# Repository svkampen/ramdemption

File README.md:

# Cyberslak PowerRAM 10MB

A 10MB RAM expansion card for the PowerBook 165c.

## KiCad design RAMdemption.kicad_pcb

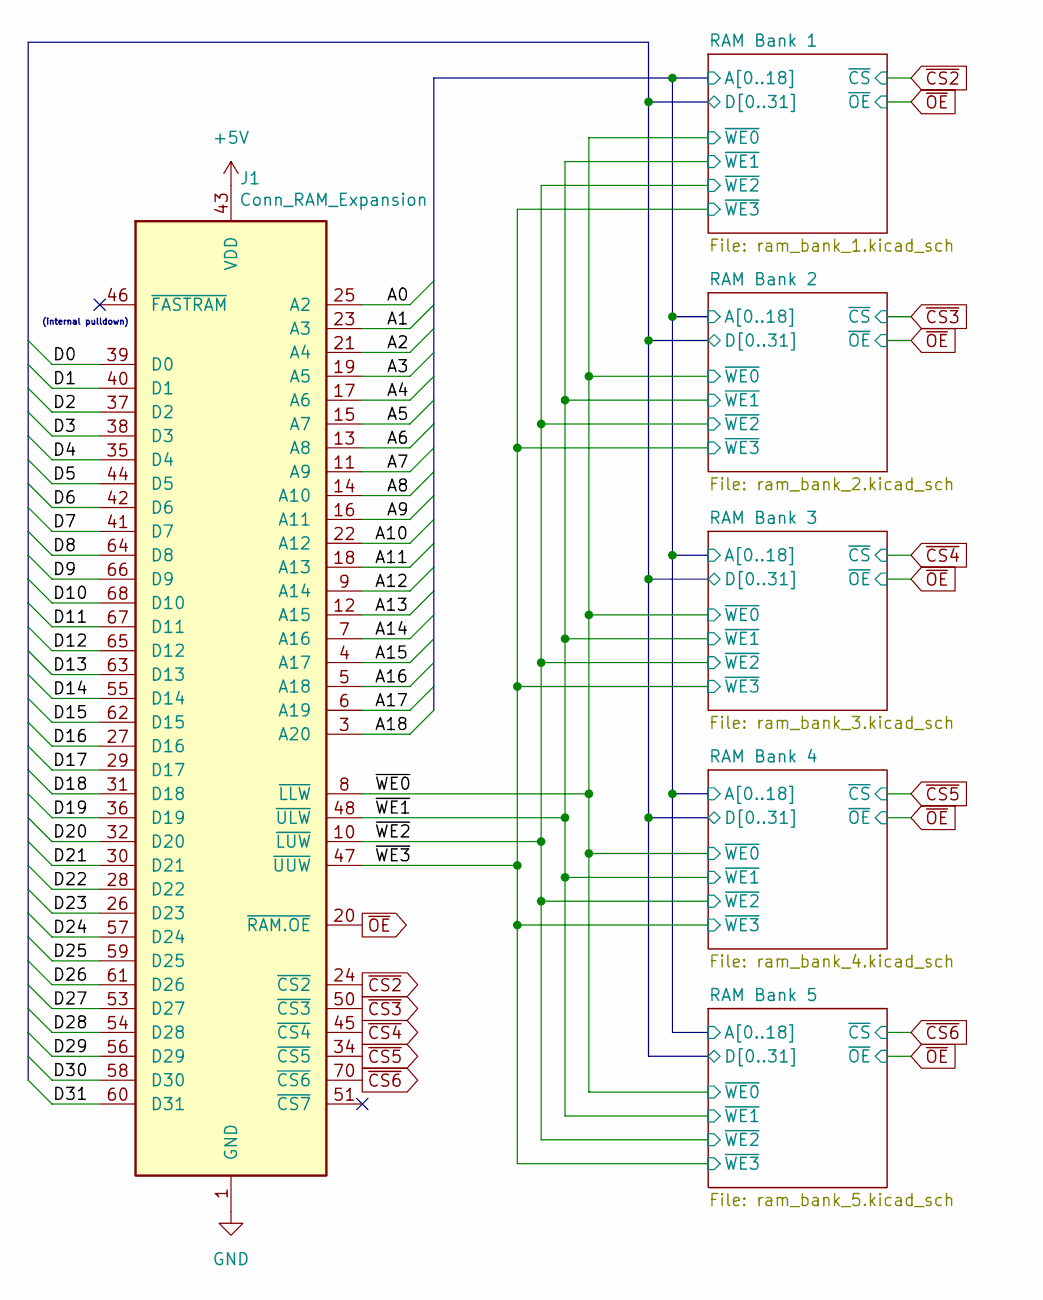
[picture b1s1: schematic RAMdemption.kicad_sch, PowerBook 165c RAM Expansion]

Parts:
J1: Conn_RAM_Expansion; TE_5-104652-7_NoHoles

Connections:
+5V: J1.43 (VDD), J1.52 (VDD); also elsewhere on the board
/RAM Bank 1/A0: J1.25 (A2); also elsewhere on the board
/RAM Bank 1/A1: J1.23 (A3); also elsewhere on the board
/RAM Bank 1/A2: J1.21 (A4); also elsewhere on the board
/RAM Bank 1/A3: J1.19 (A5); also elsewhere on the board
/RAM Bank 1/A4: J1.17 (A6); also elsewhere on the board
/RAM Bank 1/A5: J1.15 (A7); also elsewhere on the board
/RAM Bank 1/A6: J1.13 (A8); also elsewhere on the board
/RAM Bank 1/A7: J1.11 (A9); also elsewhere on the board
/RAM Bank 1/A8: J1.14 (A10); also elsewhere on the board
/RAM Bank 1/A9: J1.16 (A11); also elsewhere on the board
/RAM Bank 1/A10: J1.22 (A12); also elsewhere on the board
/RAM Bank 1/A11: J1.18 (A13); also elsewhere on the board
/RAM Bank 1/A12: J1.9 (A14); also elsewhere on the board
/RAM Bank 1/A13: J1.12 (A15); also elsewhere on the board
/RAM Bank 1/A14: J1.7 (A16); also elsewhere on the board
/RAM Bank 1/A15: J1.4 (A17); also elsewhere on the board
/RAM Bank 1/A16: J1.5 (A18); also elsewhere on the board
/RAM Bank 1/A17: J1.6 (A19); also elsewhere on the board
/RAM Bank 1/A18: J1.3 (A20); also elsewhere on the board
/RAM Bank 1/D0: J1.39 (D0); also elsewhere on the board
/RAM Bank 1/D1: J1.40 (D1); also elsewhere on the board
/RAM Bank 1/D2: J1.37 (D2); also elsewhere on the board
/RAM Bank 1/D3: J1.38 (D3); also elsewhere on the board
/RAM Bank 1/D4: J1.35 (D4); also elsewhere on the board
/RAM Bank 1/D5: J1.44 (D5); also elsewhere on the board
/RAM Bank 1/D6: J1.42 (D6); also elsewhere on the board
/RAM Bank 1/D7: J1.41 (D7); also elsewhere on the board
/RAM Bank 1/D8: J1.64 (D8); also elsewhere on the board
/RAM Bank 1/D9: J1.66 (D9); also elsewhere on the board
/RAM Bank 1/D10: J1.68 (D10); also elsewhere on the board
/RAM Bank 1/D11: J1.67 (D11); also elsewhere on the board
/RAM Bank 1/D12: J1.65 (D12); also elsewhere on the board
/RAM Bank 1/D13: J1.63 (D13); also elsewhere on the board
/RAM Bank 1/D14: J1.55 (D14); also elsewhere on the board
/RAM Bank 1/D15: J1.62 (D15); also elsewhere on the board
/RAM Bank 1/D16: J1.27 (D16); also elsewhere on the board
/RAM Bank 1/D17: J1.29 (D17); also elsewhere on the board
/RAM Bank 1/D18: J1.31 (D18); also elsewhere on the board
/RAM Bank 1/D19: J1.36 (D19); also elsewhere on the board
/RAM Bank 1/D20: J1.32 (D20); also elsewhere on the board
/RAM Bank 1/D21: J1.30 (D21); also elsewhere on the board
/RAM Bank 1/D22: J1.28 (D22); also elsewhere on the board
/RAM Bank 1/D23: J1.26 (D23); also elsewhere on the board
/RAM Bank 1/D24: J1.57 (D24); also elsewhere on the board
/RAM Bank 1/D25: J1.59 (D25); also elsewhere on the board
/RAM Bank 1/D26: J1.61 (D26); also elsewhere on the board
/RAM Bank 1/D27: J1.53 (D27); also elsewhere on the board
/RAM Bank 1/D28: J1.54 (D28); also elsewhere on the board
/RAM Bank 1/D29: J1.56 (D29); also elsewhere on the board
/RAM Bank 1/D30: J1.58 (D30); also elsewhere on the board
/RAM Bank 1/D31: J1.60 (D31); also elsewhere on the board
/~WE0: J1.8 (~LLW); also elsewhere on the board
/~WE1: J1.48 (~ULW); also elsewhere on the board
/~WE2: J1.10 (~LUW); also elsewhere on the board
/~WE3: J1.47 (~UUW); also elsewhere on the board
GND: J1.1 (GND), J1.2 (GND), J1.33 (GND), J1.69 (GND); also elsewhere on the board
~CS2: J1.24 (~CS2); also elsewhere on the board
~CS3: J1.50 (~CS3); also elsewhere on the board
~CS4: J1.45 (~CS4); also elsewhere on the board
~CS5: J1.34 (~CS5); also elsewhere on the board
~CS6: J1.70 (~CS6); also elsewhere on the board
~OE: J1.20 (~RAM.OE); also elsewhere on the board

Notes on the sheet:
(internal pulldown)

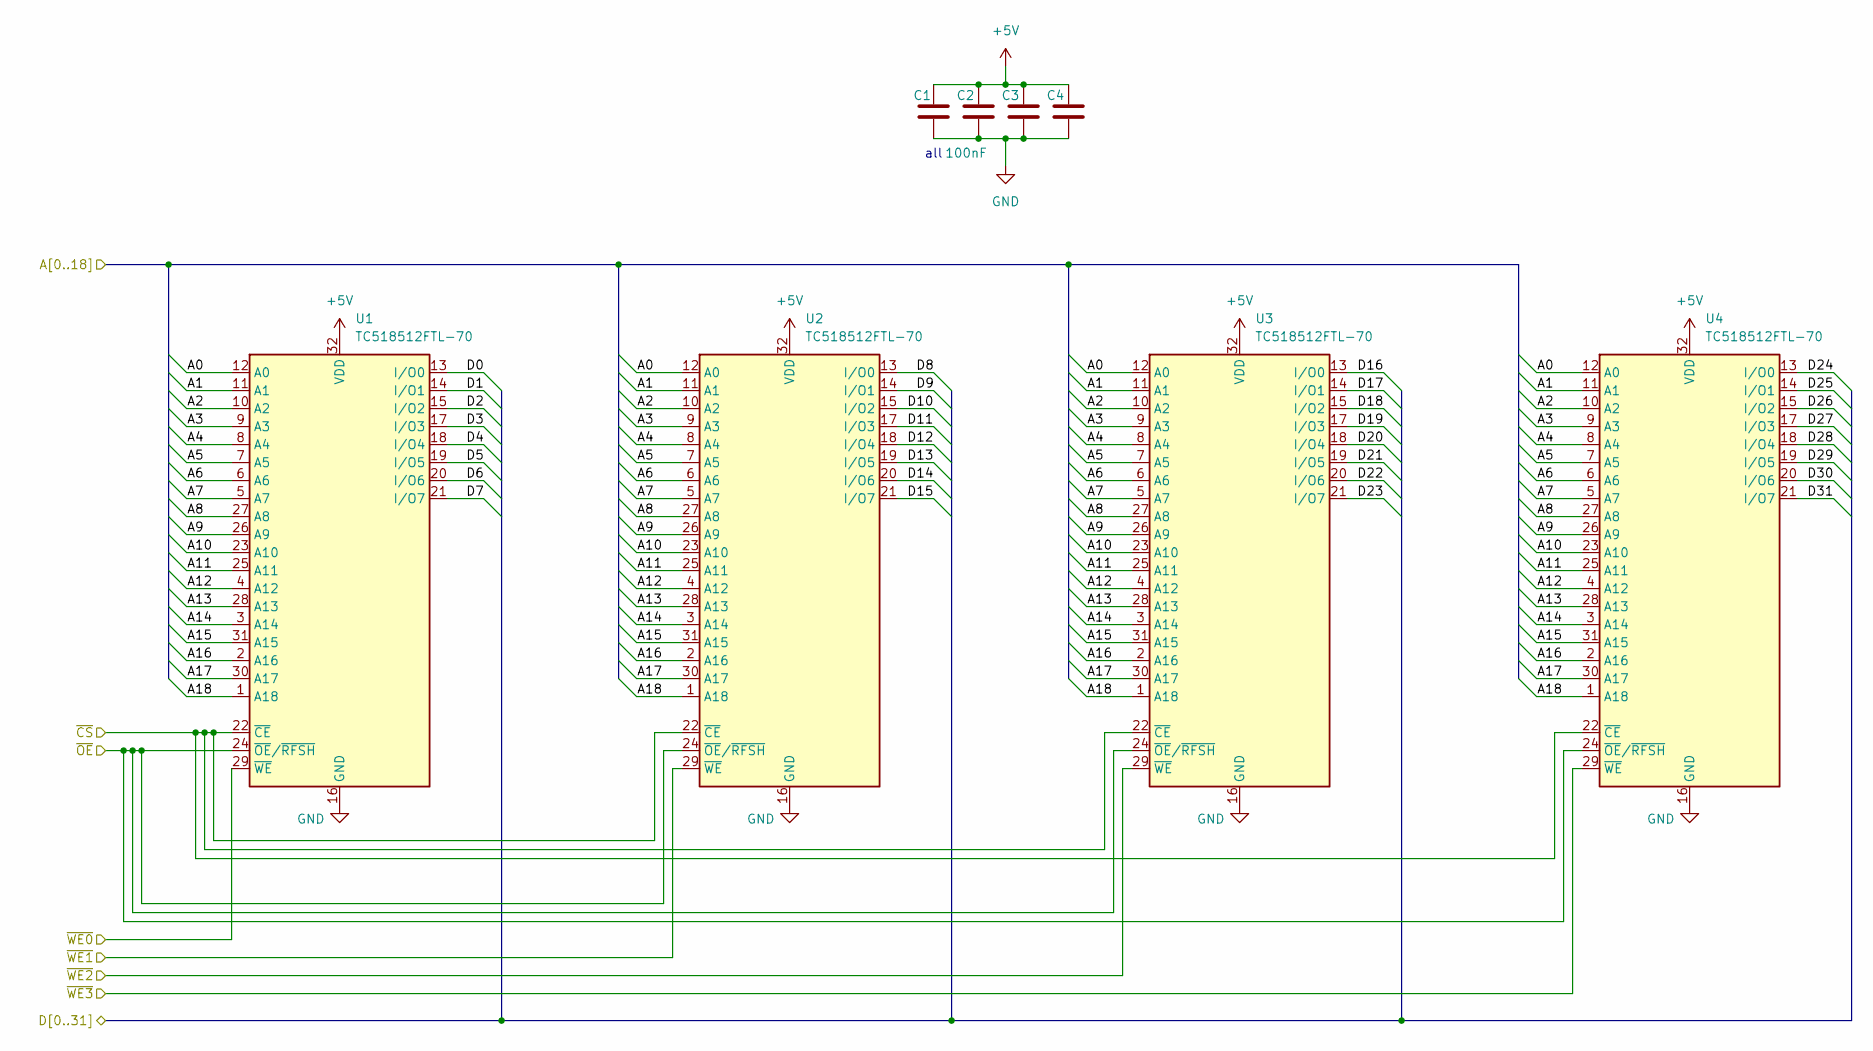
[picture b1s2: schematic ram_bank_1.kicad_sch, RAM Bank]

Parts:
C1, C2, C3, C4: 100nF; C_0805_2012Metric_Pad1.18x1.45mm_HandSolder
U1: TC518512FTL-70; TSOP-II-32_Data0
U2: TC518512FTL-70; TSOP-II-32_ReversedAddr
U3: TC518512FTL-70; TSOP-II-32_21.0x10.2mm_P1.27mm
U4: TC518512FTL-70; TSOP-II-32_ReversedAddr_Data3

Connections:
+5V: C1.1, C2.1, C3.1, C4.1, U1.32 (VDD), U2.32 (VDD), U3.32 (VDD), U4.32 (VDD); also elsewhere on the board
/RAM Bank 1/A0: U1.12 (A0), U2.12 (A0), U3.12 (A0), U4.12 (A0); also elsewhere on the board
/RAM Bank 1/A1: U1.11 (A1), U2.11 (A1), U3.11 (A1), U4.11 (A1); also elsewhere on the board
/RAM Bank 1/A2: U1.10 (A2), U2.10 (A2), U3.10 (A2), U4.10 (A2); also elsewhere on the board
/RAM Bank 1/A3: U1.9 (A3), U2.9 (A3), U3.9 (A3), U4.9 (A3); also elsewhere on the board
/RAM Bank 1/A4: U1.8 (A4), U2.8 (A4), U3.8 (A4), U4.8 (A4); also elsewhere on the board
/RAM Bank 1/A5: U1.7 (A5), U2.7 (A5), U3.7 (A5), U4.7 (A5); also elsewhere on the board
/RAM Bank 1/A6: U1.6 (A6), U2.6 (A6), U3.6 (A6), U4.6 (A6); also elsewhere on the board
/RAM Bank 1/A7: U1.5 (A7), U2.5 (A7), U3.5 (A7), U4.5 (A7); also elsewhere on the board
/RAM Bank 1/A8: U1.27 (A8), U2.27 (A8), U3.27 (A8), U4.27 (A8); also elsewhere on the board
/RAM Bank 1/A9: U1.26 (A9), U2.26 (A9), U3.26 (A9), U4.26 (A9); also elsewhere on the board
/RAM Bank 1/A10: U1.23 (A10), U2.23 (A10), U3.23 (A10), U4.23 (A10); also elsewhere on the board
/RAM Bank 1/A11: U1.25 (A11), U2.25 (A11), U3.25 (A11), U4.25 (A11); also elsewhere on the board
/RAM Bank 1/A12: U1.4 (A12), U2.4 (A12), U3.4 (A12), U4.4 (A12); also elsewhere on the board
/RAM Bank 1/A13: U1.28 (A13), U2.28 (A13), U3.28 (A13), U4.28 (A13); also elsewhere on the board
/RAM Bank 1/A14: U1.3 (A14), U2.3 (A14), U3.3 (A14), U4.3 (A14); also elsewhere on the board
/RAM Bank 1/A15: U1.31 (A15), U2.31 (A15), U3.31 (A15), U4.31 (A15); also elsewhere on the board
/RAM Bank 1/A16: U1.2 (A16), U2.2 (A16), U3.2 (A16), U4.2 (A16); also elsewhere on the board
/RAM Bank 1/A17: U1.30 (A17), U2.30 (A17), U3.30 (A17), U4.30 (A17); also elsewhere on the board
/RAM Bank 1/A18: U1.1 (A18), U2.1 (A18), U3.1 (A18), U4.1 (A18); also elsewhere on the board
/RAM Bank 1/D0: U1.13 (I/O0); also elsewhere on the board
/RAM Bank 1/D1: U1.14 (I/O1); also elsewhere on the board
/RAM Bank 1/D2: U1.15 (I/O2); also elsewhere on the board
/RAM Bank 1/D3: U1.17 (I/O3); also elsewhere on the board
/RAM Bank 1/D4: U1.18 (I/O4); also elsewhere on the board
/RAM Bank 1/D5: U1.19 (I/O5); also elsewhere on the board
/RAM Bank 1/D6: U1.20 (I/O6); also elsewhere on the board
/RAM Bank 1/D7: U1.21 (I/O7); also elsewhere on the board
/RAM Bank 1/D8: U2.13 (I/O0); also elsewhere on the board
/RAM Bank 1/D9: U2.14 (I/O1); also elsewhere on the board
/RAM Bank 1/D10: U2.15 (I/O2); also elsewhere on the board
/RAM Bank 1/D11: U2.17 (I/O3); also elsewhere on the board
/RAM Bank 1/D12: U2.18 (I/O4); also elsewhere on the board
/RAM Bank 1/D13: U2.19 (I/O5); also elsewhere on the board
/RAM Bank 1/D14: U2.20 (I/O6); also elsewhere on the board
/RAM Bank 1/D15: U2.21 (I/O7); also elsewhere on the board
/RAM Bank 1/D16: U3.13 (I/O0); also elsewhere on the board
/RAM Bank 1/D17: U3.14 (I/O1); also elsewhere on the board
/RAM Bank 1/D18: U3.15 (I/O2); also elsewhere on the board
/RAM Bank 1/D19: U3.17 (I/O3); also elsewhere on the board
/RAM Bank 1/D20: U3.18 (I/O4); also elsewhere on the board
/RAM Bank 1/D21: U3.19 (I/O5); also elsewhere on the board
/RAM Bank 1/D22: U3.20 (I/O6); also elsewhere on the board
/RAM Bank 1/D23: U3.21 (I/O7); also elsewhere on the board
/RAM Bank 1/D24: U4.13 (I/O0); also elsewhere on the board
/RAM Bank 1/D25: U4.14 (I/O1); also elsewhere on the board
/RAM Bank 1/D26: U4.15 (I/O2); also elsewhere on the board
/RAM Bank 1/D27: U4.17 (I/O3); also elsewhere on the board
/RAM Bank 1/D28: U4.18 (I/O4); also elsewhere on the board
/RAM Bank 1/D29: U4.19 (I/O5); also elsewhere on the board
/RAM Bank 1/D30: U4.20 (I/O6); also elsewhere on the board
/RAM Bank 1/D31: U4.21 (I/O7); also elsewhere on the board
/~WE0: U1.29 (~WE); also elsewhere on the board
/~WE1: U2.29 (~WE); also elsewhere on the board
/~WE2: U3.29 (~WE); also elsewhere on the board
/~WE3: U4.29 (~WE); also elsewhere on the board
GND: C1.2, C2.2, C3.2, C4.2, U1.16 (GND), U2.16 (GND), U3.16 (GND), U4.16 (GND); also elsewhere on the board
~CS2: U1.22 (~CE), U2.22 (~CE), U3.22 (~CE), U4.22 (~CE); also elsewhere on the board
~OE: U1.24 (~OE/~RFSH), U2.24 (~OE/~RFSH), U3.24 (~OE/~RFSH), U4.24 (~OE/~RFSH); also elsewhere on the board

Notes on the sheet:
all

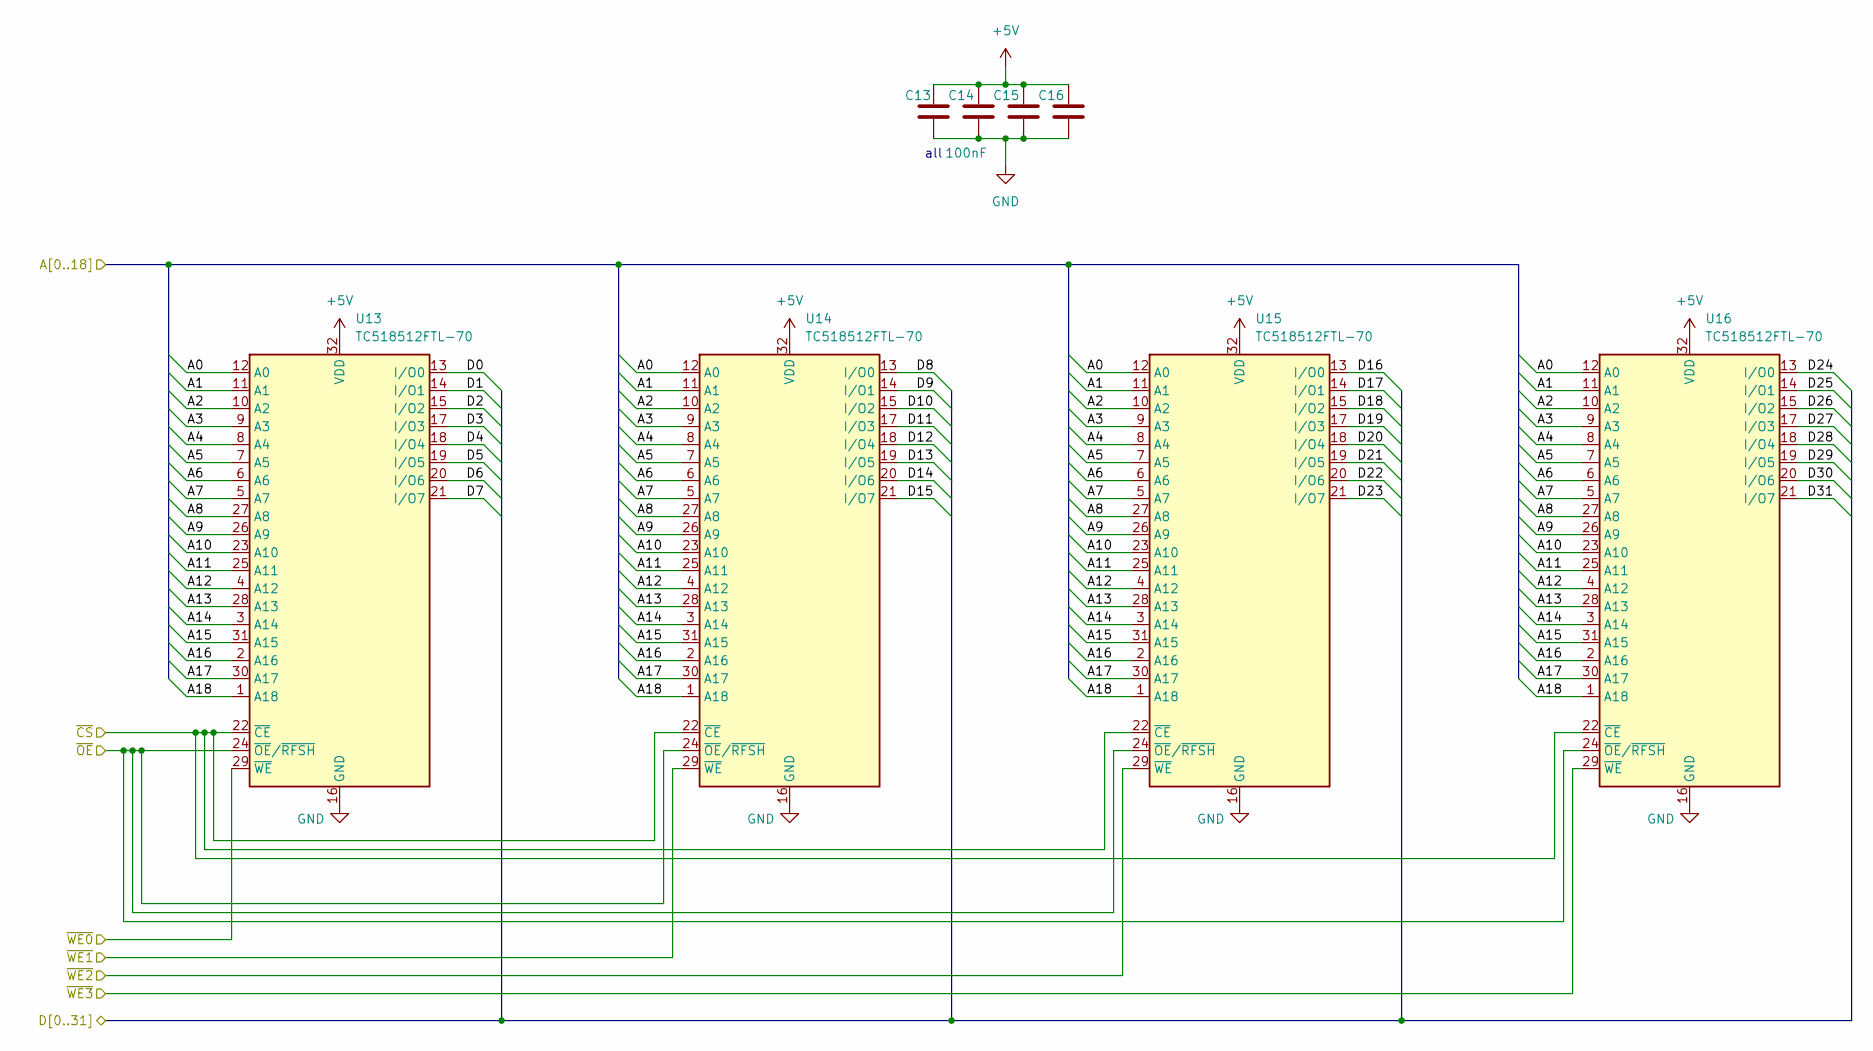
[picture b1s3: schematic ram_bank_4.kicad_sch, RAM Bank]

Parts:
C13, C14, C15, C16: 100nF; C_0805_2012Metric_Pad1.18x1.45mm_HandSolder
U13: TC518512FTL-70; TSOP-II-32_Data0
U14: TC518512FTL-70; TSOP-II-32_ReversedAddr
U15: TC518512FTL-70; TSOP-II-32_21.0x10.2mm_P1.27mm
U16: TC518512FTL-70; TSOP-II-NormalAddr-Data3

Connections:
+5V: C13.1, C14.1, C15.1, C16.1, U13.32 (VDD), U14.32 (VDD), U15.32 (VDD), U16.32 (VDD); also elsewhere on the board
/RAM Bank 1/A0: U13.12 (A0), U14.12 (A0), U15.12 (A0), U16.12 (A0); also elsewhere on the board
/RAM Bank 1/A1: U13.11 (A1), U14.11 (A1), U15.11 (A1), U16.11 (A1); also elsewhere on the board
/RAM Bank 1/A2: U13.10 (A2), U14.10 (A2), U15.10 (A2), U16.10 (A2); also elsewhere on the board
/RAM Bank 1/A3: U13.9 (A3), U14.9 (A3), U15.9 (A3), U16.9 (A3); also elsewhere on the board
/RAM Bank 1/A4: U13.8 (A4), U14.8 (A4), U15.8 (A4), U16.8 (A4); also elsewhere on the board
/RAM Bank 1/A5: U13.7 (A5), U14.7 (A5), U15.7 (A5), U16.7 (A5); also elsewhere on the board
/RAM Bank 1/A6: U13.6 (A6), U14.6 (A6), U15.6 (A6), U16.6 (A6); also elsewhere on the board
/RAM Bank 1/A7: U13.5 (A7), U14.5 (A7), U15.5 (A7), U16.5 (A7); also elsewhere on the board
/RAM Bank 1/A8: U13.27 (A8), U14.27 (A8), U15.27 (A8), U16.27 (A8); also elsewhere on the board
/RAM Bank 1/A9: U13.26 (A9), U14.26 (A9), U15.26 (A9), U16.26 (A9); also elsewhere on the board
/RAM Bank 1/A10: U13.23 (A10), U14.23 (A10), U15.23 (A10), U16.23 (A10); also elsewhere on the board
/RAM Bank 1/A11: U13.25 (A11), U14.25 (A11), U15.25 (A11), U16.25 (A11); also elsewhere on the board
/RAM Bank 1/A12: U13.4 (A12), U14.4 (A12), U15.4 (A12), U16.4 (A12); also elsewhere on the board
/RAM Bank 1/A13: U13.28 (A13), U14.28 (A13), U15.28 (A13), U16.28 (A13); also elsewhere on the board
/RAM Bank 1/A14: U13.3 (A14), U14.3 (A14), U15.3 (A14), U16.3 (A14); also elsewhere on the board
/RAM Bank 1/A15: U13.31 (A15), U14.31 (A15), U15.31 (A15), U16.31 (A15); also elsewhere on the board
/RAM Bank 1/A16: U13.2 (A16), U14.2 (A16), U15.2 (A16), U16.2 (A16); also elsewhere on the board
/RAM Bank 1/A17: U13.30 (A17), U14.30 (A17), U15.30 (A17), U16.30 (A17); also elsewhere on the board
/RAM Bank 1/A18: U13.1 (A18), U14.1 (A18), U15.1 (A18), U16.1 (A18); also elsewhere on the board
/RAM Bank 1/D0: U13.13 (I/O0); also elsewhere on the board
/RAM Bank 1/D1: U13.14 (I/O1); also elsewhere on the board
/RAM Bank 1/D2: U13.15 (I/O2); also elsewhere on the board
/RAM Bank 1/D3: U13.17 (I/O3); also elsewhere on the board
/RAM Bank 1/D4: U13.18 (I/O4); also elsewhere on the board
/RAM Bank 1/D5: U13.19 (I/O5); also elsewhere on the board
/RAM Bank 1/D6: U13.20 (I/O6); also elsewhere on the board
/RAM Bank 1/D7: U13.21 (I/O7); also elsewhere on the board
/RAM Bank 1/D8: U14.13 (I/O0); also elsewhere on the board
/RAM Bank 1/D9: U14.14 (I/O1); also elsewhere on the board
/RAM Bank 1/D10: U14.15 (I/O2); also elsewhere on the board
/RAM Bank 1/D11: U14.17 (I/O3); also elsewhere on the board
/RAM Bank 1/D12: U14.18 (I/O4); also elsewhere on the board
/RAM Bank 1/D13: U14.19 (I/O5); also elsewhere on the board
/RAM Bank 1/D14: U14.20 (I/O6); also elsewhere on the board
/RAM Bank 1/D15: U14.21 (I/O7); also elsewhere on the board
/RAM Bank 1/D16: U15.13 (I/O0); also elsewhere on the board
/RAM Bank 1/D17: U15.14 (I/O1); also elsewhere on the board
/RAM Bank 1/D18: U15.15 (I/O2); also elsewhere on the board
/RAM Bank 1/D19: U15.17 (I/O3); also elsewhere on the board
/RAM Bank 1/D20: U15.18 (I/O4); also elsewhere on the board
/RAM Bank 1/D21: U15.19 (I/O5); also elsewhere on the board
/RAM Bank 1/D22: U15.20 (I/O6); also elsewhere on the board
/RAM Bank 1/D23: U15.21 (I/O7); also elsewhere on the board
/RAM Bank 1/D24: U16.13 (I/O0); also elsewhere on the board
/RAM Bank 1/D25: U16.14 (I/O1); also elsewhere on the board
/RAM Bank 1/D26: U16.15 (I/O2); also elsewhere on the board
/RAM Bank 1/D27: U16.17 (I/O3); also elsewhere on the board
/RAM Bank 1/D28: U16.18 (I/O4); also elsewhere on the board
/RAM Bank 1/D29: U16.19 (I/O5); also elsewhere on the board
/RAM Bank 1/D30: U16.20 (I/O6); also elsewhere on the board
/RAM Bank 1/D31: U16.21 (I/O7); also elsewhere on the board
/~WE0: U13.29 (~WE); also elsewhere on the board
/~WE1: U14.29 (~WE); also elsewhere on the board
/~WE2: U15.29 (~WE); also elsewhere on the board
/~WE3: U16.29 (~WE); also elsewhere on the board
GND: C13.2, C14.2, C15.2, C16.2, U13.16 (GND), U14.16 (GND), U15.16 (GND), U16.16 (GND); also elsewhere on the board
~CS5: U13.22 (~CE), U14.22 (~CE), U15.22 (~CE), U16.22 (~CE); also elsewhere on the board
~OE: U13.24 (~OE/~RFSH), U14.24 (~OE/~RFSH), U15.24 (~OE/~RFSH), U16.24 (~OE/~RFSH); also elsewhere on the board

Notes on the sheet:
all

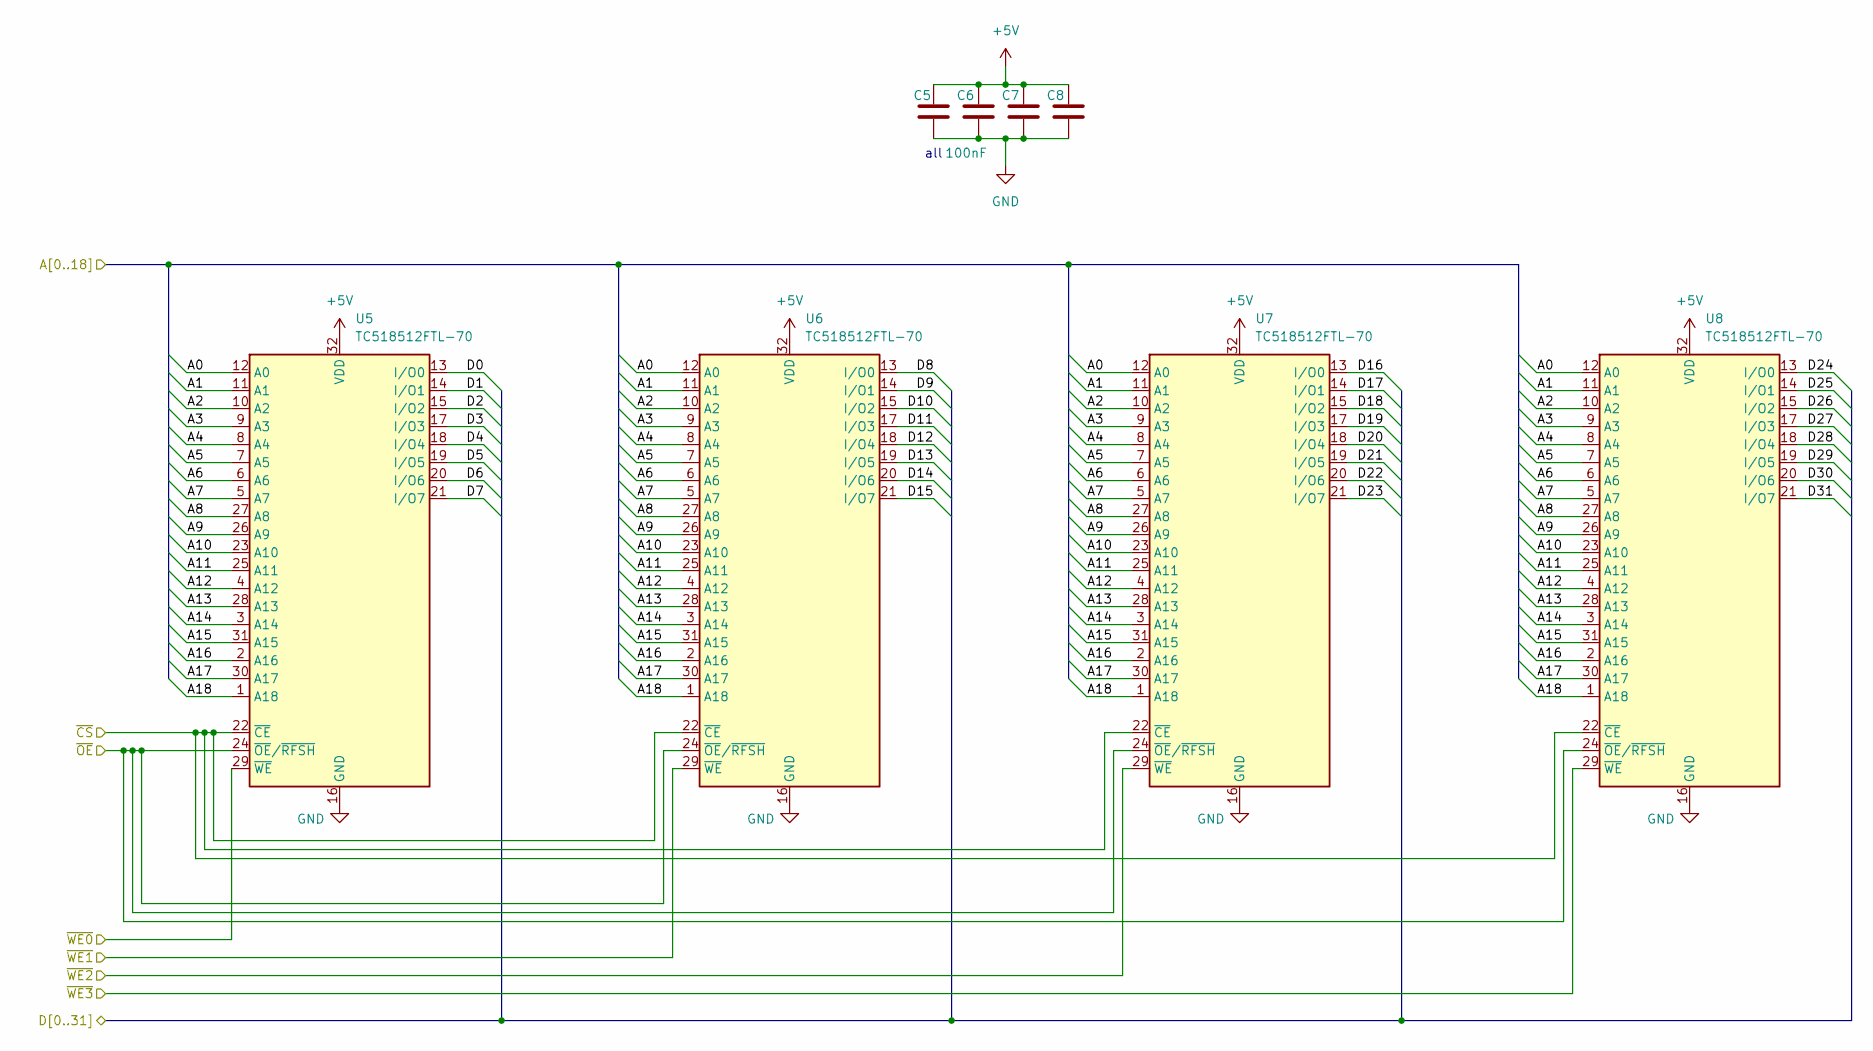
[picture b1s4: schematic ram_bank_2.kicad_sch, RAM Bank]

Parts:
C5, C6, C7, C8: 100nF; C_0805_2012Metric_Pad1.18x1.45mm_HandSolder
U5: TC518512FTL-70; TSOP-II-32_Data0
U6: TC518512FTL-70; TSOP-II-32_ReversedAddr
U7: TC518512FTL-70; TSOP-II-32_21.0x10.2mm_P1.27mm
U8: TC518512FTL-70; TSOP-II-NormalAddr-Data3

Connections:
+5V: C5.1, C6.1, C7.1, C8.1, U5.32 (VDD), U6.32 (VDD), U7.32 (VDD), U8.32 (VDD); also elsewhere on the board
/RAM Bank 1/A0: U5.12 (A0), U6.12 (A0), U7.12 (A0), U8.12 (A0); also elsewhere on the board
/RAM Bank 1/A1: U5.11 (A1), U6.11 (A1), U7.11 (A1), U8.11 (A1); also elsewhere on the board
/RAM Bank 1/A2: U5.10 (A2), U6.10 (A2), U7.10 (A2), U8.10 (A2); also elsewhere on the board
/RAM Bank 1/A3: U5.9 (A3), U6.9 (A3), U7.9 (A3), U8.9 (A3); also elsewhere on the board
/RAM Bank 1/A4: U5.8 (A4), U6.8 (A4), U7.8 (A4), U8.8 (A4); also elsewhere on the board
/RAM Bank 1/A5: U5.7 (A5), U6.7 (A5), U7.7 (A5), U8.7 (A5); also elsewhere on the board
/RAM Bank 1/A6: U5.6 (A6), U6.6 (A6), U7.6 (A6), U8.6 (A6); also elsewhere on the board
/RAM Bank 1/A7: U5.5 (A7), U6.5 (A7), U7.5 (A7), U8.5 (A7); also elsewhere on the board
/RAM Bank 1/A8: U5.27 (A8), U6.27 (A8), U7.27 (A8), U8.27 (A8); also elsewhere on the board
/RAM Bank 1/A9: U5.26 (A9), U6.26 (A9), U7.26 (A9), U8.26 (A9); also elsewhere on the board
/RAM Bank 1/A10: U5.23 (A10), U6.23 (A10), U7.23 (A10), U8.23 (A10); also elsewhere on the board
/RAM Bank 1/A11: U5.25 (A11), U6.25 (A11), U7.25 (A11), U8.25 (A11); also elsewhere on the board
/RAM Bank 1/A12: U5.4 (A12), U6.4 (A12), U7.4 (A12), U8.4 (A12); also elsewhere on the board
/RAM Bank 1/A13: U5.28 (A13), U6.28 (A13), U7.28 (A13), U8.28 (A13); also elsewhere on the board
/RAM Bank 1/A14: U5.3 (A14), U6.3 (A14), U7.3 (A14), U8.3 (A14); also elsewhere on the board
/RAM Bank 1/A15: U5.31 (A15), U6.31 (A15), U7.31 (A15), U8.31 (A15); also elsewhere on the board
/RAM Bank 1/A16: U5.2 (A16), U6.2 (A16), U7.2 (A16), U8.2 (A16); also elsewhere on the board
/RAM Bank 1/A17: U5.30 (A17), U6.30 (A17), U7.30 (A17), U8.30 (A17); also elsewhere on the board
/RAM Bank 1/A18: U5.1 (A18), U6.1 (A18), U7.1 (A18), U8.1 (A18); also elsewhere on the board
/RAM Bank 1/D0: U5.13 (I/O0); also elsewhere on the board
/RAM Bank 1/D1: U5.14 (I/O1); also elsewhere on the board
/RAM Bank 1/D2: U5.15 (I/O2); also elsewhere on the board
/RAM Bank 1/D3: U5.17 (I/O3); also elsewhere on the board
/RAM Bank 1/D4: U5.18 (I/O4); also elsewhere on the board
/RAM Bank 1/D5: U5.19 (I/O5); also elsewhere on the board
/RAM Bank 1/D6: U5.20 (I/O6); also elsewhere on the board
/RAM Bank 1/D7: U5.21 (I/O7); also elsewhere on the board
/RAM Bank 1/D8: U6.13 (I/O0); also elsewhere on the board
/RAM Bank 1/D9: U6.14 (I/O1); also elsewhere on the board
/RAM Bank 1/D10: U6.15 (I/O2); also elsewhere on the board
/RAM Bank 1/D11: U6.17 (I/O3); also elsewhere on the board
/RAM Bank 1/D12: U6.18 (I/O4); also elsewhere on the board
/RAM Bank 1/D13: U6.19 (I/O5); also elsewhere on the board
/RAM Bank 1/D14: U6.20 (I/O6); also elsewhere on the board
/RAM Bank 1/D15: U6.21 (I/O7); also elsewhere on the board
/RAM Bank 1/D16: U7.13 (I/O0); also elsewhere on the board
/RAM Bank 1/D17: U7.14 (I/O1); also elsewhere on the board
/RAM Bank 1/D18: U7.15 (I/O2); also elsewhere on the board
/RAM Bank 1/D19: U7.17 (I/O3); also elsewhere on the board
/RAM Bank 1/D20: U7.18 (I/O4); also elsewhere on the board
/RAM Bank 1/D21: U7.19 (I/O5); also elsewhere on the board
/RAM Bank 1/D22: U7.20 (I/O6); also elsewhere on the board
/RAM Bank 1/D23: U7.21 (I/O7); also elsewhere on the board
/RAM Bank 1/D24: U8.13 (I/O0); also elsewhere on the board
/RAM Bank 1/D25: U8.14 (I/O1); also elsewhere on the board
/RAM Bank 1/D26: U8.15 (I/O2); also elsewhere on the board
/RAM Bank 1/D27: U8.17 (I/O3); also elsewhere on the board
/RAM Bank 1/D28: U8.18 (I/O4); also elsewhere on the board
/RAM Bank 1/D29: U8.19 (I/O5); also elsewhere on the board
/RAM Bank 1/D30: U8.20 (I/O6); also elsewhere on the board
/RAM Bank 1/D31: U8.21 (I/O7); also elsewhere on the board
/~WE0: U5.29 (~WE); also elsewhere on the board
/~WE1: U6.29 (~WE); also elsewhere on the board
/~WE2: U7.29 (~WE); also elsewhere on the board
/~WE3: U8.29 (~WE); also elsewhere on the board
GND: C5.2, C6.2, C7.2, C8.2, U5.16 (GND), U6.16 (GND), U7.16 (GND), U8.16 (GND); also elsewhere on the board
~CS3: U5.22 (~CE), U6.22 (~CE), U7.22 (~CE), U8.22 (~CE); also elsewhere on the board
~OE: U5.24 (~OE/~RFSH), U6.24 (~OE/~RFSH), U7.24 (~OE/~RFSH), U8.24 (~OE/~RFSH); also elsewhere on the board

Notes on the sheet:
all

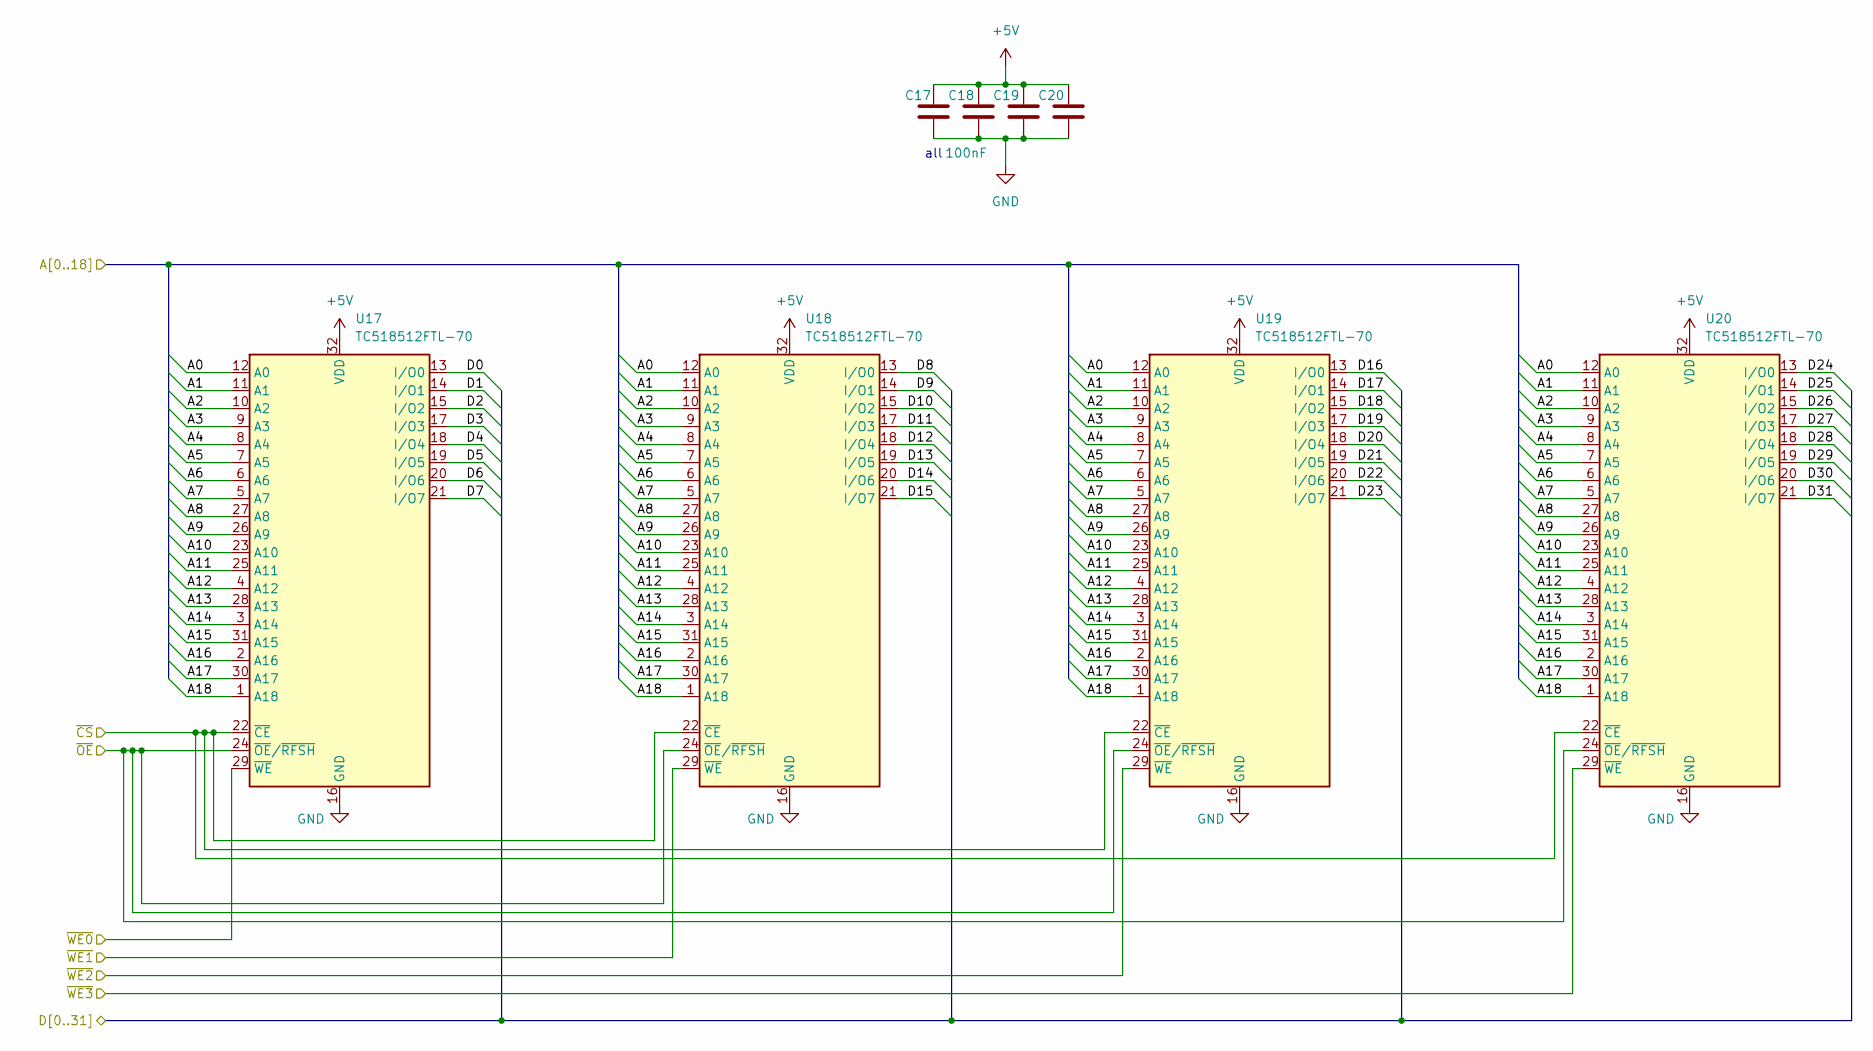
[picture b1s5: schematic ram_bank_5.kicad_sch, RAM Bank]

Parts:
C17, C18, C19, C20: 100nF; C_0805_2012Metric_Pad1.18x1.45mm_HandSolder
U17: TC518512FTL-70; TSOP-II-32_Data0
U18: TC518512FTL-70; TSOP-II-32_ReversedAddr
U19: TC518512FTL-70; TSOP-II-32_21.0x10.2mm_P1.27mm
U20: TC518512FTL-70; TSOP-II-32_ReversedAddr_Data3

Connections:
+5V: C17.1, C18.1, C19.1, C20.1, U17.32 (VDD), U18.32 (VDD), U19.32 (VDD), U20.32 (VDD); also elsewhere on the board
/RAM Bank 1/A0: U17.12 (A0), U18.12 (A0), U19.12 (A0), U20.12 (A0); also elsewhere on the board
/RAM Bank 1/A1: U17.11 (A1), U18.11 (A1), U19.11 (A1), U20.11 (A1); also elsewhere on the board
/RAM Bank 1/A2: U17.10 (A2), U18.10 (A2), U19.10 (A2), U20.10 (A2); also elsewhere on the board
/RAM Bank 1/A3: U17.9 (A3), U18.9 (A3), U19.9 (A3), U20.9 (A3); also elsewhere on the board
/RAM Bank 1/A4: U17.8 (A4), U18.8 (A4), U19.8 (A4), U20.8 (A4); also elsewhere on the board
/RAM Bank 1/A5: U17.7 (A5), U18.7 (A5), U19.7 (A5), U20.7 (A5); also elsewhere on the board
/RAM Bank 1/A6: U17.6 (A6), U18.6 (A6), U19.6 (A6), U20.6 (A6); also elsewhere on the board
/RAM Bank 1/A7: U17.5 (A7), U18.5 (A7), U19.5 (A7), U20.5 (A7); also elsewhere on the board
/RAM Bank 1/A8: U17.27 (A8), U18.27 (A8), U19.27 (A8), U20.27 (A8); also elsewhere on the board
/RAM Bank 1/A9: U17.26 (A9), U18.26 (A9), U19.26 (A9), U20.26 (A9); also elsewhere on the board
/RAM Bank 1/A10: U17.23 (A10), U18.23 (A10), U19.23 (A10), U20.23 (A10); also elsewhere on the board
/RAM Bank 1/A11: U17.25 (A11), U18.25 (A11), U19.25 (A11), U20.25 (A11); also elsewhere on the board
/RAM Bank 1/A12: U17.4 (A12), U18.4 (A12), U19.4 (A12), U20.4 (A12); also elsewhere on the board
/RAM Bank 1/A13: U17.28 (A13), U18.28 (A13), U19.28 (A13), U20.28 (A13); also elsewhere on the board
/RAM Bank 1/A14: U17.3 (A14), U18.3 (A14), U19.3 (A14), U20.3 (A14); also elsewhere on the board
/RAM Bank 1/A15: U17.31 (A15), U18.31 (A15), U19.31 (A15), U20.31 (A15); also elsewhere on the board
/RAM Bank 1/A16: U17.2 (A16), U18.2 (A16), U19.2 (A16), U20.2 (A16); also elsewhere on the board
/RAM Bank 1/A17: U17.30 (A17), U18.30 (A17), U19.30 (A17), U20.30 (A17); also elsewhere on the board
/RAM Bank 1/A18: U17.1 (A18), U18.1 (A18), U19.1 (A18), U20.1 (A18); also elsewhere on the board
/RAM Bank 1/D0: U17.13 (I/O0); also elsewhere on the board
/RAM Bank 1/D1: U17.14 (I/O1); also elsewhere on the board
/RAM Bank 1/D2: U17.15 (I/O2); also elsewhere on the board
/RAM Bank 1/D3: U17.17 (I/O3); also elsewhere on the board
/RAM Bank 1/D4: U17.18 (I/O4); also elsewhere on the board
/RAM Bank 1/D5: U17.19 (I/O5); also elsewhere on the board
/RAM Bank 1/D6: U17.20 (I/O6); also elsewhere on the board
/RAM Bank 1/D7: U17.21 (I/O7); also elsewhere on the board
/RAM Bank 1/D8: U18.13 (I/O0); also elsewhere on the board
/RAM Bank 1/D9: U18.14 (I/O1); also elsewhere on the board
/RAM Bank 1/D10: U18.15 (I/O2); also elsewhere on the board
/RAM Bank 1/D11: U18.17 (I/O3); also elsewhere on the board
/RAM Bank 1/D12: U18.18 (I/O4); also elsewhere on the board
/RAM Bank 1/D13: U18.19 (I/O5); also elsewhere on the board
/RAM Bank 1/D14: U18.20 (I/O6); also elsewhere on the board
/RAM Bank 1/D15: U18.21 (I/O7); also elsewhere on the board
/RAM Bank 1/D16: U19.13 (I/O0); also elsewhere on the board
/RAM Bank 1/D17: U19.14 (I/O1); also elsewhere on the board
/RAM Bank 1/D18: U19.15 (I/O2); also elsewhere on the board
/RAM Bank 1/D19: U19.17 (I/O3); also elsewhere on the board
/RAM Bank 1/D20: U19.18 (I/O4); also elsewhere on the board
/RAM Bank 1/D21: U19.19 (I/O5); also elsewhere on the board
/RAM Bank 1/D22: U19.20 (I/O6); also elsewhere on the board
/RAM Bank 1/D23: U19.21 (I/O7); also elsewhere on the board
/RAM Bank 1/D24: U20.13 (I/O0); also elsewhere on the board
/RAM Bank 1/D25: U20.14 (I/O1); also elsewhere on the board
/RAM Bank 1/D26: U20.15 (I/O2); also elsewhere on the board
/RAM Bank 1/D27: U20.17 (I/O3); also elsewhere on the board
/RAM Bank 1/D28: U20.18 (I/O4); also elsewhere on the board
/RAM Bank 1/D29: U20.19 (I/O5); also elsewhere on the board
/RAM Bank 1/D30: U20.20 (I/O6); also elsewhere on the board
/RAM Bank 1/D31: U20.21 (I/O7); also elsewhere on the board
/~WE0: U17.29 (~WE); also elsewhere on the board
/~WE1: U18.29 (~WE); also elsewhere on the board
/~WE2: U19.29 (~WE); also elsewhere on the board
/~WE3: U20.29 (~WE); also elsewhere on the board
GND: C17.2, C18.2, C19.2, C20.2, U17.16 (GND), U18.16 (GND), U19.16 (GND), U20.16 (GND); also elsewhere on the board
~CS6: U17.22 (~CE), U18.22 (~CE), U19.22 (~CE), U20.22 (~CE); also elsewhere on the board
~OE: U17.24 (~OE/~RFSH), U18.24 (~OE/~RFSH), U19.24 (~OE/~RFSH), U20.24 (~OE/~RFSH); also elsewhere on the board

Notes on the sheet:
all
